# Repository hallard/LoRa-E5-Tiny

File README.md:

# LoRa-E5-Tiny

Based on [LoRa-E5](https://www.seeedstudio.com/LoRa-E5-Wireless-Module-p-4745.html) from Seedstudio, but I wanted something really Tiny so I removed loy of stuff and left only JTAG prog, Serial and I2C Stemma QWIIC connector, and of course cell coin handler.

> :eyes: take a look on this excellent [reading](https://www.rs-online.com/designspark/can-i-prolong-my-coin-cell-battery-life-with-a-capacitor) on how to use capacitor to prolong cell coin batteries and understand the risk. I will use for EU8868 so for peaks approx 40mA, 3 times less than in the article so I guess it could works with 2 x 220uF or 470uF capacitors. Challenge would be to find them in 1206 footprint format.

I'm using mainly to flash custom firmware in it, and not using AT default firmware.

> :warning: **These boards have been received** they works as expected but stil not tried with cell coin powering

## Challenges

With this consumption [issue](https://forum.rakwireless.com/t/rak3172-too-much-consumption-in-transmit-eu868/4781) discovered on LoRa-E5 boards (but also on RAK3172) I'm not confident it will works on Cell Coin CR2450 battery even if I added 2 330uF capacitors on 3.3V rail.

## Features

- LoRa-E5 Module
- FTDI SMD 6 pads edge connector (:warning: **use 3.3V FTDI One, not 5V**)
- JTAG SMD 6 pads edge connector to flash module (PA13-SWDIO / PA14-SWCLK / PB3-SWO / RESET)
- Green Led on PB13
- Red Led on PA9
- 2 Tactile Switches (boot and reset)
- u-FL Antenna connector
- Stemma QWIIC I2C connector
- 2 x 1206 footprint for big capacitors see [reading](https://www.rs-online.com/designspark/can-i-prolong-my-coin-cell-battery-life-with-a-capacitor)
- CR2450 Cell coin battery size
- CR2450 battery holder

## Detailed Description

No specific documentation for now, it's just a kind of wiring helper as schematic.

I also assume that you are familiar with all LoRaWAN stuff, all setup/infrastructure/network server/provisionning and other are out of scope of this repository.

## Schematics

## Boards 

You can order board on [oshpark](https://oshpark.com). 

- [V1.0](https://oshpark.com/shared_projects/xUa1Y94Z) 

It's a pitty after several discuss with OSHPark that I can't have any rewards for each people ordering my boards, this would allow me to order free PCB for shared projects and create new ones. For information my shared boards generated a total of **$285 162.00** orders at PCBs.io in 4 years, not bad at all :-), but looks like they have gone :sob:

Hoping one day OSHparks will thanks me giving them this market. 

### Assembled boards

**Top & bottom side V1.0**

<!--

-->

### Bill Of Material

Nothing fancy, due to size constraint, components are 0603/1206 and can be ordered almost anywhere (digikey, mouser, radiospare, ...). 
use only what you need dependings on what you want to do. 

> :memo: I2C pullup may not needed, most QWIIC/Steamma boards have their own. 

Check Seeed format [BOM](https://github.com/hallard/LoRa-E5-Tiny/blob/main/LoRa-E5-Tiny-BOM.xlsx) File, check on [Seeed OPL](https://www.seeedstudio.com/opl.html) for manufacturer SKU match.

### Test Board out of factory stock 

When the boards are from factory, default AT firmware is flashed and thus we have the possibility to test the board before flashing custom firmware and maily also get defaults keys from device.

To do so, connect a 3V3 FTDI Type USB/Serial to access Serial Console 

> :warning: **Do not use 5V configured FTDI** 

I personnaly use these one for [Sparkun](https://www.sparkfun.com/products/14050) but you can find clones anywhere on the Web.

Once done open Serial terminal (the one from FTDI Serial Port) configured as `9600` BPS `8N1`, no flow control, echo typed characters and set to CR+LF for enter key, press reset button and you should be able to see banner

- Connect FTDI on the 6 pins edge header of the board (if PCB is 2mm thickness should works without soldering)
- use them a terminal application and open the port on your computer corresponding to the FTDI device
- set terminal settings to 9600 bauds 8 bits no parity 1 stop bit (8N1)

Once done open Serial terminal (the one from FTDI Serial Port) configured as `9600` BPS `8N1`, no flow control, echo typed characters and set to CR+LF for enter key

Then type `AT` command to see if the LoRa board answer, in this example the board answered `+AT: OK` which is correct
```
AT 
+AT: OK
```

Now get the device version
```
AT+VER 
+VER: 4.0.11
```

Now get the device information 
```
AT+ID  
+ID: DevAddr, 24:90:08:93
+ID: DevEui, 2C:F7:F1:20:24:90:08:93
+ID: AppEui, 80:00:00:00:00:00:00:06
```

I'm using [TTN](https://www.thethingsnetwork.org/) for testing so please follow excellent RAK guide on how to provision your device onto TTN [here](https://docs.rakwireless.com/Product-Categories/WisDuo/RAK3172-Module/Quickstart/#connecting-to-the-things-network-ttn)

In our case we will use the AppKey generated from TTN when provisionning device, just provision your device onto TTN, get the key and put into the device as follow with command `AT+KEY=APPKEY` in our case AppKey is `B7536DCEFB1EBC4AB9871293F6FA7DB5`
```
AT+KEY=APPKEY,"B7536DCEFB1EBC4AB9871293F6FA7DB5" 
+KEY: APPKEY B7536DCEFB1EBC4AB9871293F6FA7DB5
```

Set ADR + Frequency Plan EU868 + OTAA
```
AT+ADR=ON   
+ADR: ON
AT+DR=EU868  
+DR: EU868
AT+MODE=LWOTAA 
+MODE: LWOTAA
```

Check Frequency Plan
```
AT+DR=SCHEME 
+DR: EU868
+DR: EU868 DR0  SF12 BW125K 
+DR: EU868 DR1  SF11 BW125K 
+DR: EU868 DR2  SF10 BW125K 
+DR: EU868 DR3  SF9  BW125K 
+DR: EU868 DR4  SF8  BW125K 
+DR: EU868 DR5  SF7  BW125K 
+DR: EU868 DR6  SF7  BW250K 
+DR: EU868 DR7  FSK  50kbps 
+DR: EU868 DR8  RFU
+DR: EU868 DR9  RFU
+DR: EU868 DR10 RFU
+DR: EU868 DR11 RFU
+DR: EU868 DR12 RFU
+DR: EU868 DR13 RFU
+DR: EU868 DR14 RFU
+DR: EU868 DR15 RFU
```

Now time to join (be sure device is provisioned on TTN and you have a TTN gateway around)
```
AT+JOIN 
+JOIN: Start
+JOIN: NORMAL
+JOIN: Network joined
+JOIN: NetID 000013 DevAddr 26:0B:63:94
+JOIN: Done
```

Now send confirmed Hello World message
```
AT+CMSG="Hello World"  
+CMSG: Start
+CMSG: Wait ACK
+CMSG: FPENDING
+CMSG: ACK Received
+CMSG: RXWIN1, RSSI -40, SNR 5.0
+CMSG: Done
```

### Compile and flash Firmware

You can flash the board with excellent [mbed-os](https://os.mbed.com/mbed-os/) framework. 
Easy way is to use [mbed studio IDE](https://os.mbed.com/studio/). 
We added this board into [stm32customtargets](https://github.com/ARMmbed/stm32customtargets), don't hesitate to read the [readme](https://github.com/ARMmbed/stm32customtargets/blob/master/README.md). 
Finally the main firmware [mbed-os-example-lorawan](https://github.com/ARMmbed/mbed-os-example-lorawan) program.

Once IDE installed: 

- use `file` / `import program` and them import the example with URL `https://github.com/ARMmbed/mbed-os-example-lorawan`
- right click in the project name and select `Add Library` and enter `https://github.com/ARMmbed/stm32customtargets`
- open the file `custom_targets.json` from folder `stm32customtargets` and copy whole contents
- paste copied contents in the main root folder file `custom_targets.json` (yes replace the whole file) 
- open the file `mbed_app.json` and change parameters on the section `target_overrides`
    - LoRaWAN parameters such as frequency plan, OTAA, Duty Cycle, ...
    - replace keys with the ones you got from above step `lora.device-eui`, `lora.application-eui` and `lora.application-key`
- add the following section near the end of the file `mbed_app.json`.

```json
        "LORA_E5_TINY": {
            "stm32wl-lora-driver.rf_switch_config": 2,
            "stm32wl-lora-driver.debug_rx": "LED1",
            "stm32wl-lora-driver.debug_tx": "LED2",
            "stm32wl-lora-driver.debug_invert": 1
        }
```

Then on IDE select target "LORA_E5_TINY", build and flash with your favorite programmer (I'm using STLink) with GND/SWDIO/SWDCLK/RESET connected. 

Pay attention, that 1st time you need to erase SeeeStudio original firmware, make sure the Read Out Protection of the device is AA. If it is shown as BB, select AA and click Apply. See the end of this [section](https://wiki.seeedstudio.com/LoRa_E5_Dev_Board/#24-modify-your-device-eui-application-eui-application-key-and-your-lorawan-region) on how to do that with STM32CubeProgrammer.

### Build and Flash

From IDE you can build the example. If you plug your STLink while project opened, mbed ide will ask you if you want to set it up for this project/target, once approved you can compile, flash and even debug from mbed ide (need some tools installed, [read](https://os.mbed.com/docs/mbed-studio/current/monitor-debug/debugging-with-mbed-studio.html), very nice.

<!---->

You can also see logs with the FTDI adapter and any Serial terminal set to 115200 bauds 8 bits no parity 1 stop bit (8N1)

```
Mbed LoRaWANStack initialized 
 CONFIRMED message retries : 3 
 Adaptive data  rate (ADR) - Enabled 
 Connection - In Progress ...
 Connection - Successful 
 Dummy Sensor Value = 3 
 23 bytes scheduled for transmission 
 Message Sent to Network Server 
 Dummy Sensor Value = 5 
 23 bytes scheduled for transmission 
 Message Sent to Network Server 
 Dummy Sensor Value = 7 
 23 bytes scheduled for transmission 
```

Green LED will be on when on receive mode and Red when sending data.

## License

This work is licensed under a [Creative Commons Attribution-NonCommercial 4.0 International License](http://creativecommons.org/licenses/by-nc/4.0/)

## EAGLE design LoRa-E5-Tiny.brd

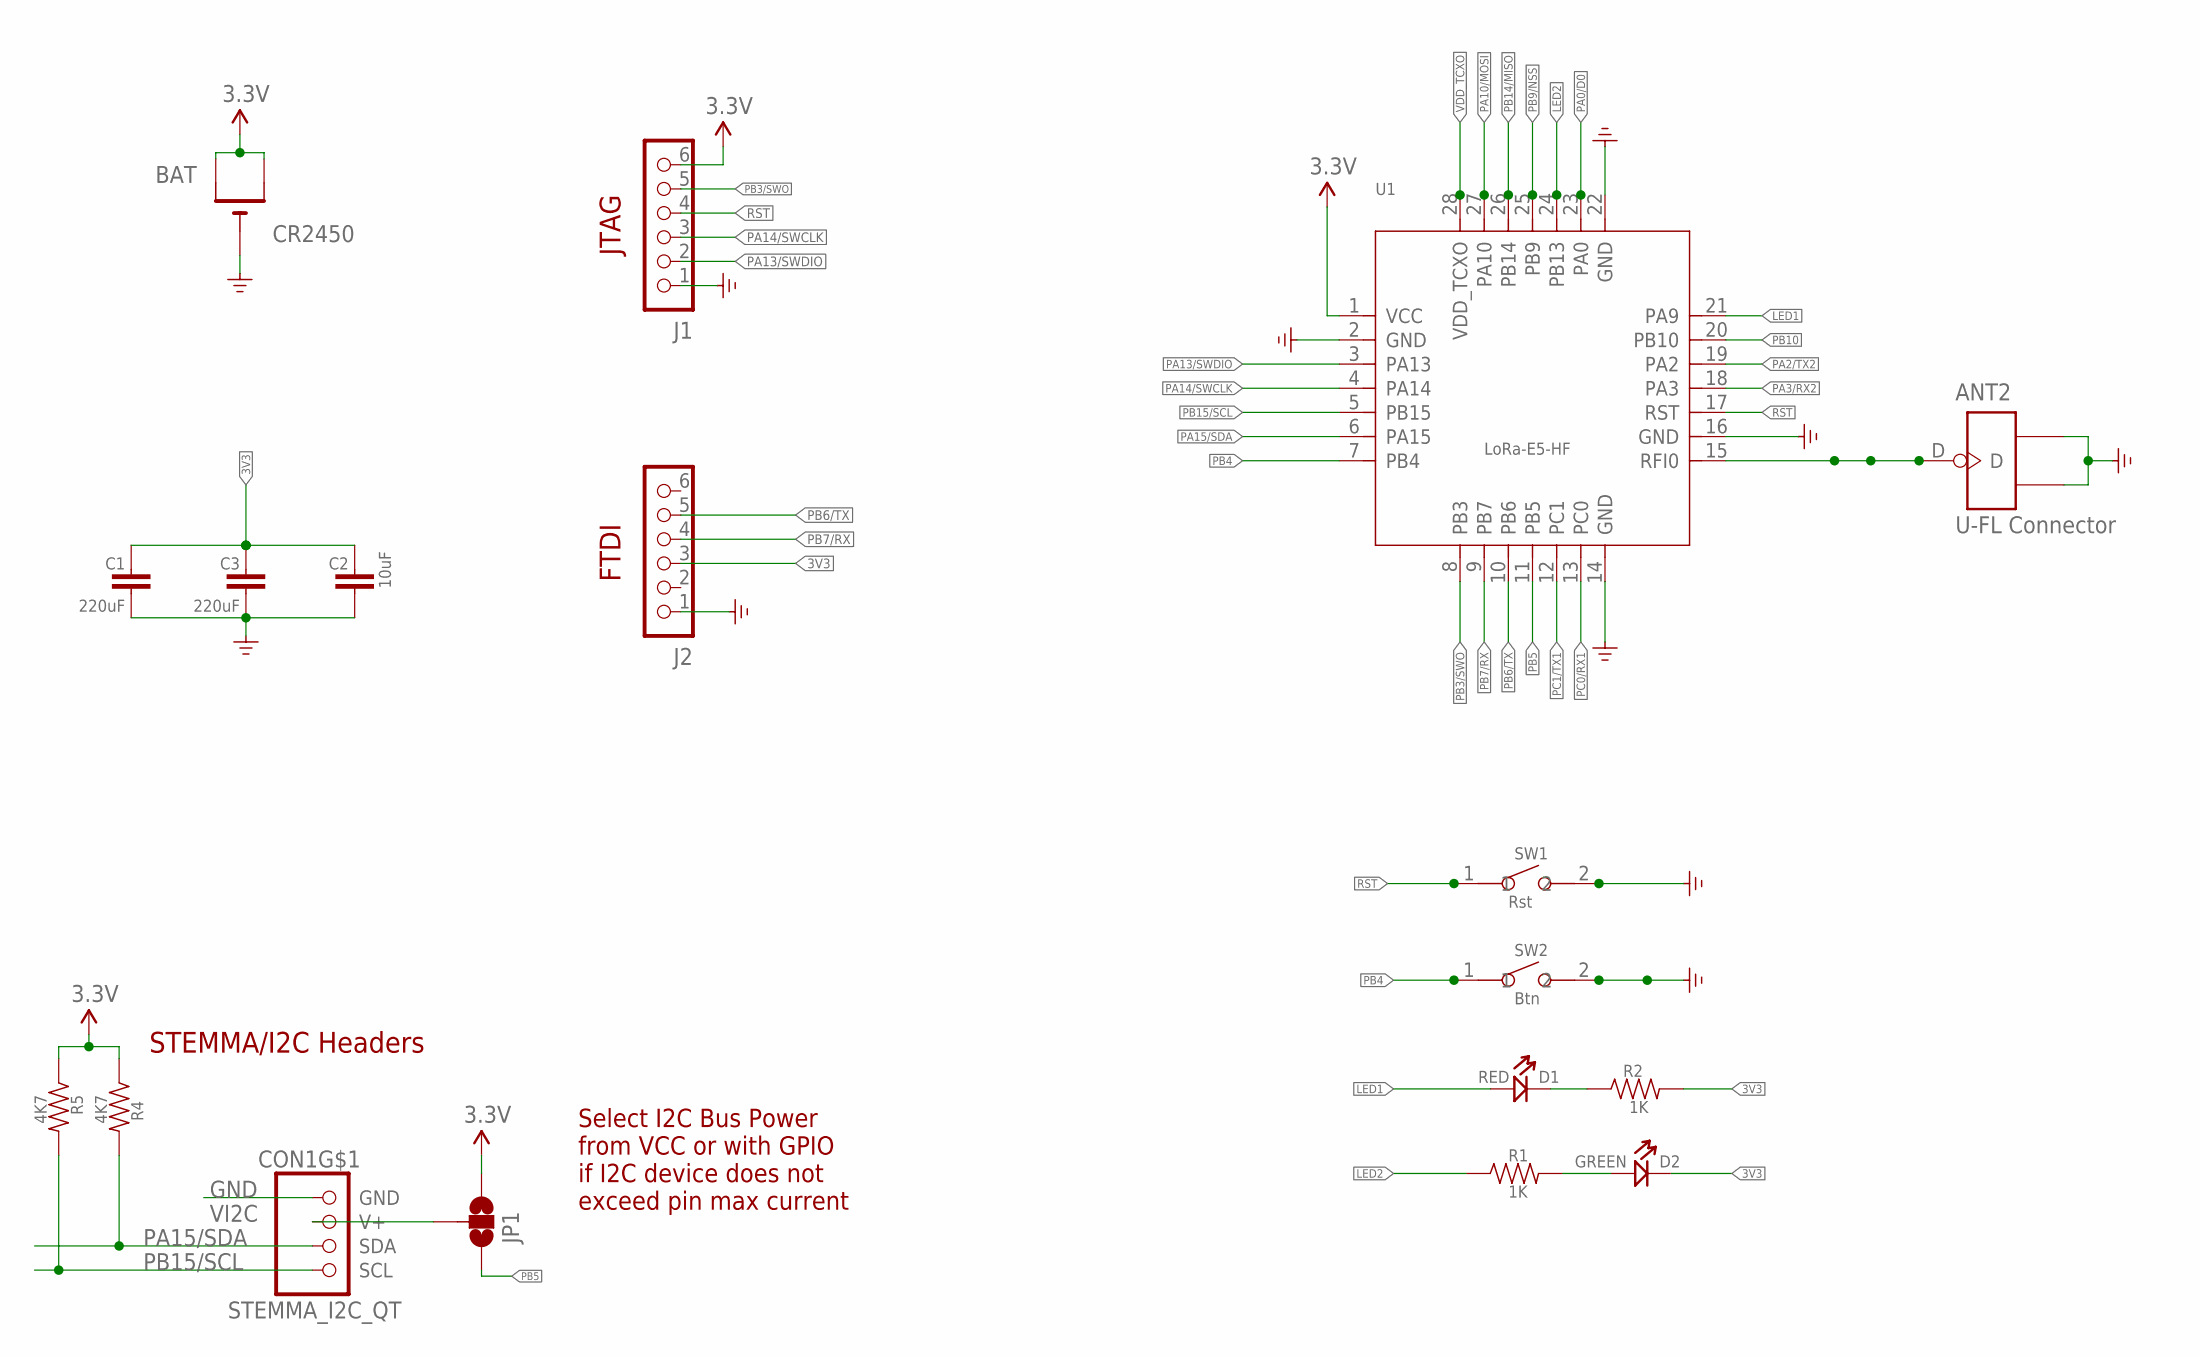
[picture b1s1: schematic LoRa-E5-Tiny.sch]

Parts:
ANT2: U-FL Connector; U-FL3P-SMD-2.6X2.6X1.0MM
BAT: CR2450; CR2450-THM
C1, C3: 220uF; 1206
C2: 10uF; 0603-CAP
CON1: STEMMA_I2C_QT; JST_SH4
D1: RED; LED-0805
D2: GREEN; LED-0805
J1: JTAG; M1X06_PAD
J2: FTDI; M1X06_PAD
JP1: JUMPER-SMT_3_NO_NO-SILK; SMT-JUMPER_3_NO_NO-SILK
R1, R2: 1K; 0603-RES
R4, R5: 4K7; 0603-RES
SW1: Rst; SW2-2.6-3.0X2.5X1.2+0.4MM
SW2: Btn; SW2-2.6-3.0X2.5X1.2+0.4MM
U1: LoRa-E5-HF; MOUDLE28P-1.25-12X12X2.5MM

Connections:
3V3: BAT.+1 (+), BAT.+2 (+1), C1.2, C2.2, C3.2, D2.-, J1.6, J2.3, JP1.1, R2.2, R4.1, R5.1, U1.1 (VCC)
GND: ANT2.GND1, ANT2.GND2, BAT.GND (-), C1.1, C2.1, C3.1, CON1.1 (GND), J1.1, J2.1, SW1.2, SW2.2, U1.2 (GND), U1.14 (GND), U1.16 (GND), U1.22 (GND)
LED1: D1.+, U1.21 (PA9)
LED2: R1.1, U1.24 (PB13)
unnamed: D2.+, R1.2
unnamed: D1.-, R2.1
PA0/D0: U1.23 (PA0)
PA2/TX2: U1.19 (PA2)
PA3/RX2: U1.18 (PA3)
PA10/MOSI: U1.27 (PA10)
PA13/SWDIO: J1.2, U1.3 (PA13)
PA14/SWCLK: J1.3, U1.4 (PA14)
PA15/SDA: CON1.3 (SDA), R4.2, U1.6 (PA15)
PB3/SWO: J1.5, U1.8 (PB3)
PB4: SW2.1, U1.7 (PB4)
PB5: JP1.3, U1.11 (PB5)
PB6/TX: J2.5, U1.10 (PB6)
PB7/RX: J2.4, U1.9 (PB7)
PB9/NSS: U1.25 (PB9)
PB10: U1.20 (PB10)
PB14/MISO: U1.26 (PB14)
PB15/SCL: CON1.4 (SCL), R5.2, U1.5 (PB15)
PC0/RX1: U1.13 (PC0)
PC1/TX1: U1.12 (PC1)
RF: ANT2.D, U1.15 (RFI0)
RST: J1.4, SW1.1, U1.17 (RST)
VDD_TCXO: U1.28 (VDD_TCXO)
VI2C: CON1.2 (V+), JP1.2

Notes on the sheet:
STEMMA/I2C Headers
JTAG
FTDI
Select I2C Bus Power from VCC or with GPIO if I2C device does not exceed pin max current

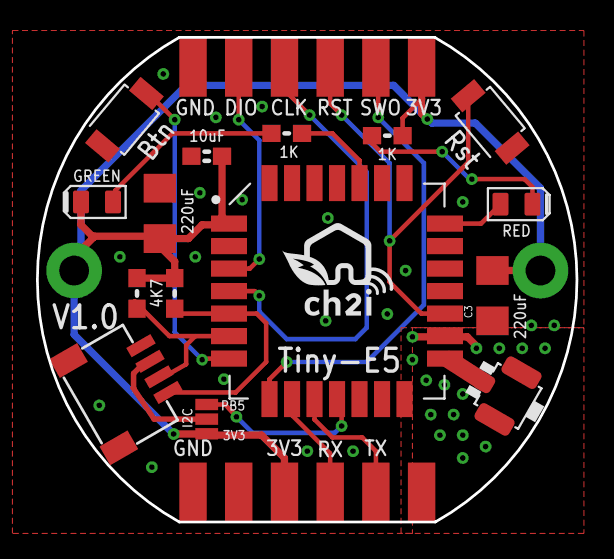
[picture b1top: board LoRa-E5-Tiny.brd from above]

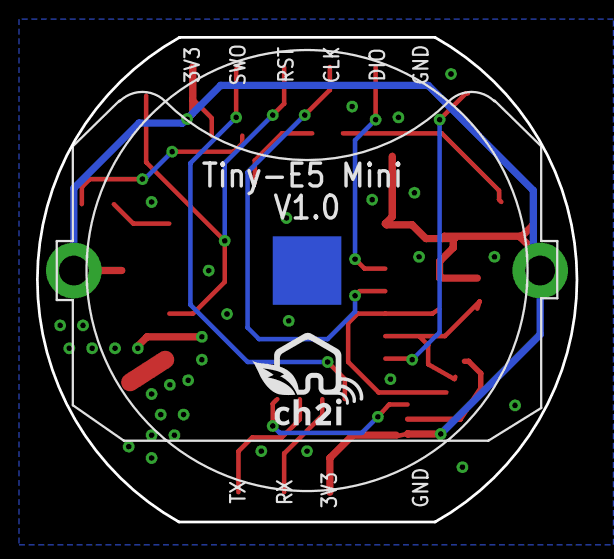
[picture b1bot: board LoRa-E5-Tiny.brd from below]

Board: 2 copper layers, 30.0 x 26.9 mm, 20 parts (2 on the bottom side), 18 nets.

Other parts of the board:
U$1, U$2: LOGO_C2I_015

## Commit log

2021-08-18 fix power

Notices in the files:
parts and their libraries:
microbuilder: This work is placed in the public domain, and may be freely used for commercial and non-commercial work with the following conditions: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
SparkFun-Jumpers: Licensing: Creative Commons ShareAlike 4.0 International - https://creativecommons.org/licenses/by-sa/4.0
